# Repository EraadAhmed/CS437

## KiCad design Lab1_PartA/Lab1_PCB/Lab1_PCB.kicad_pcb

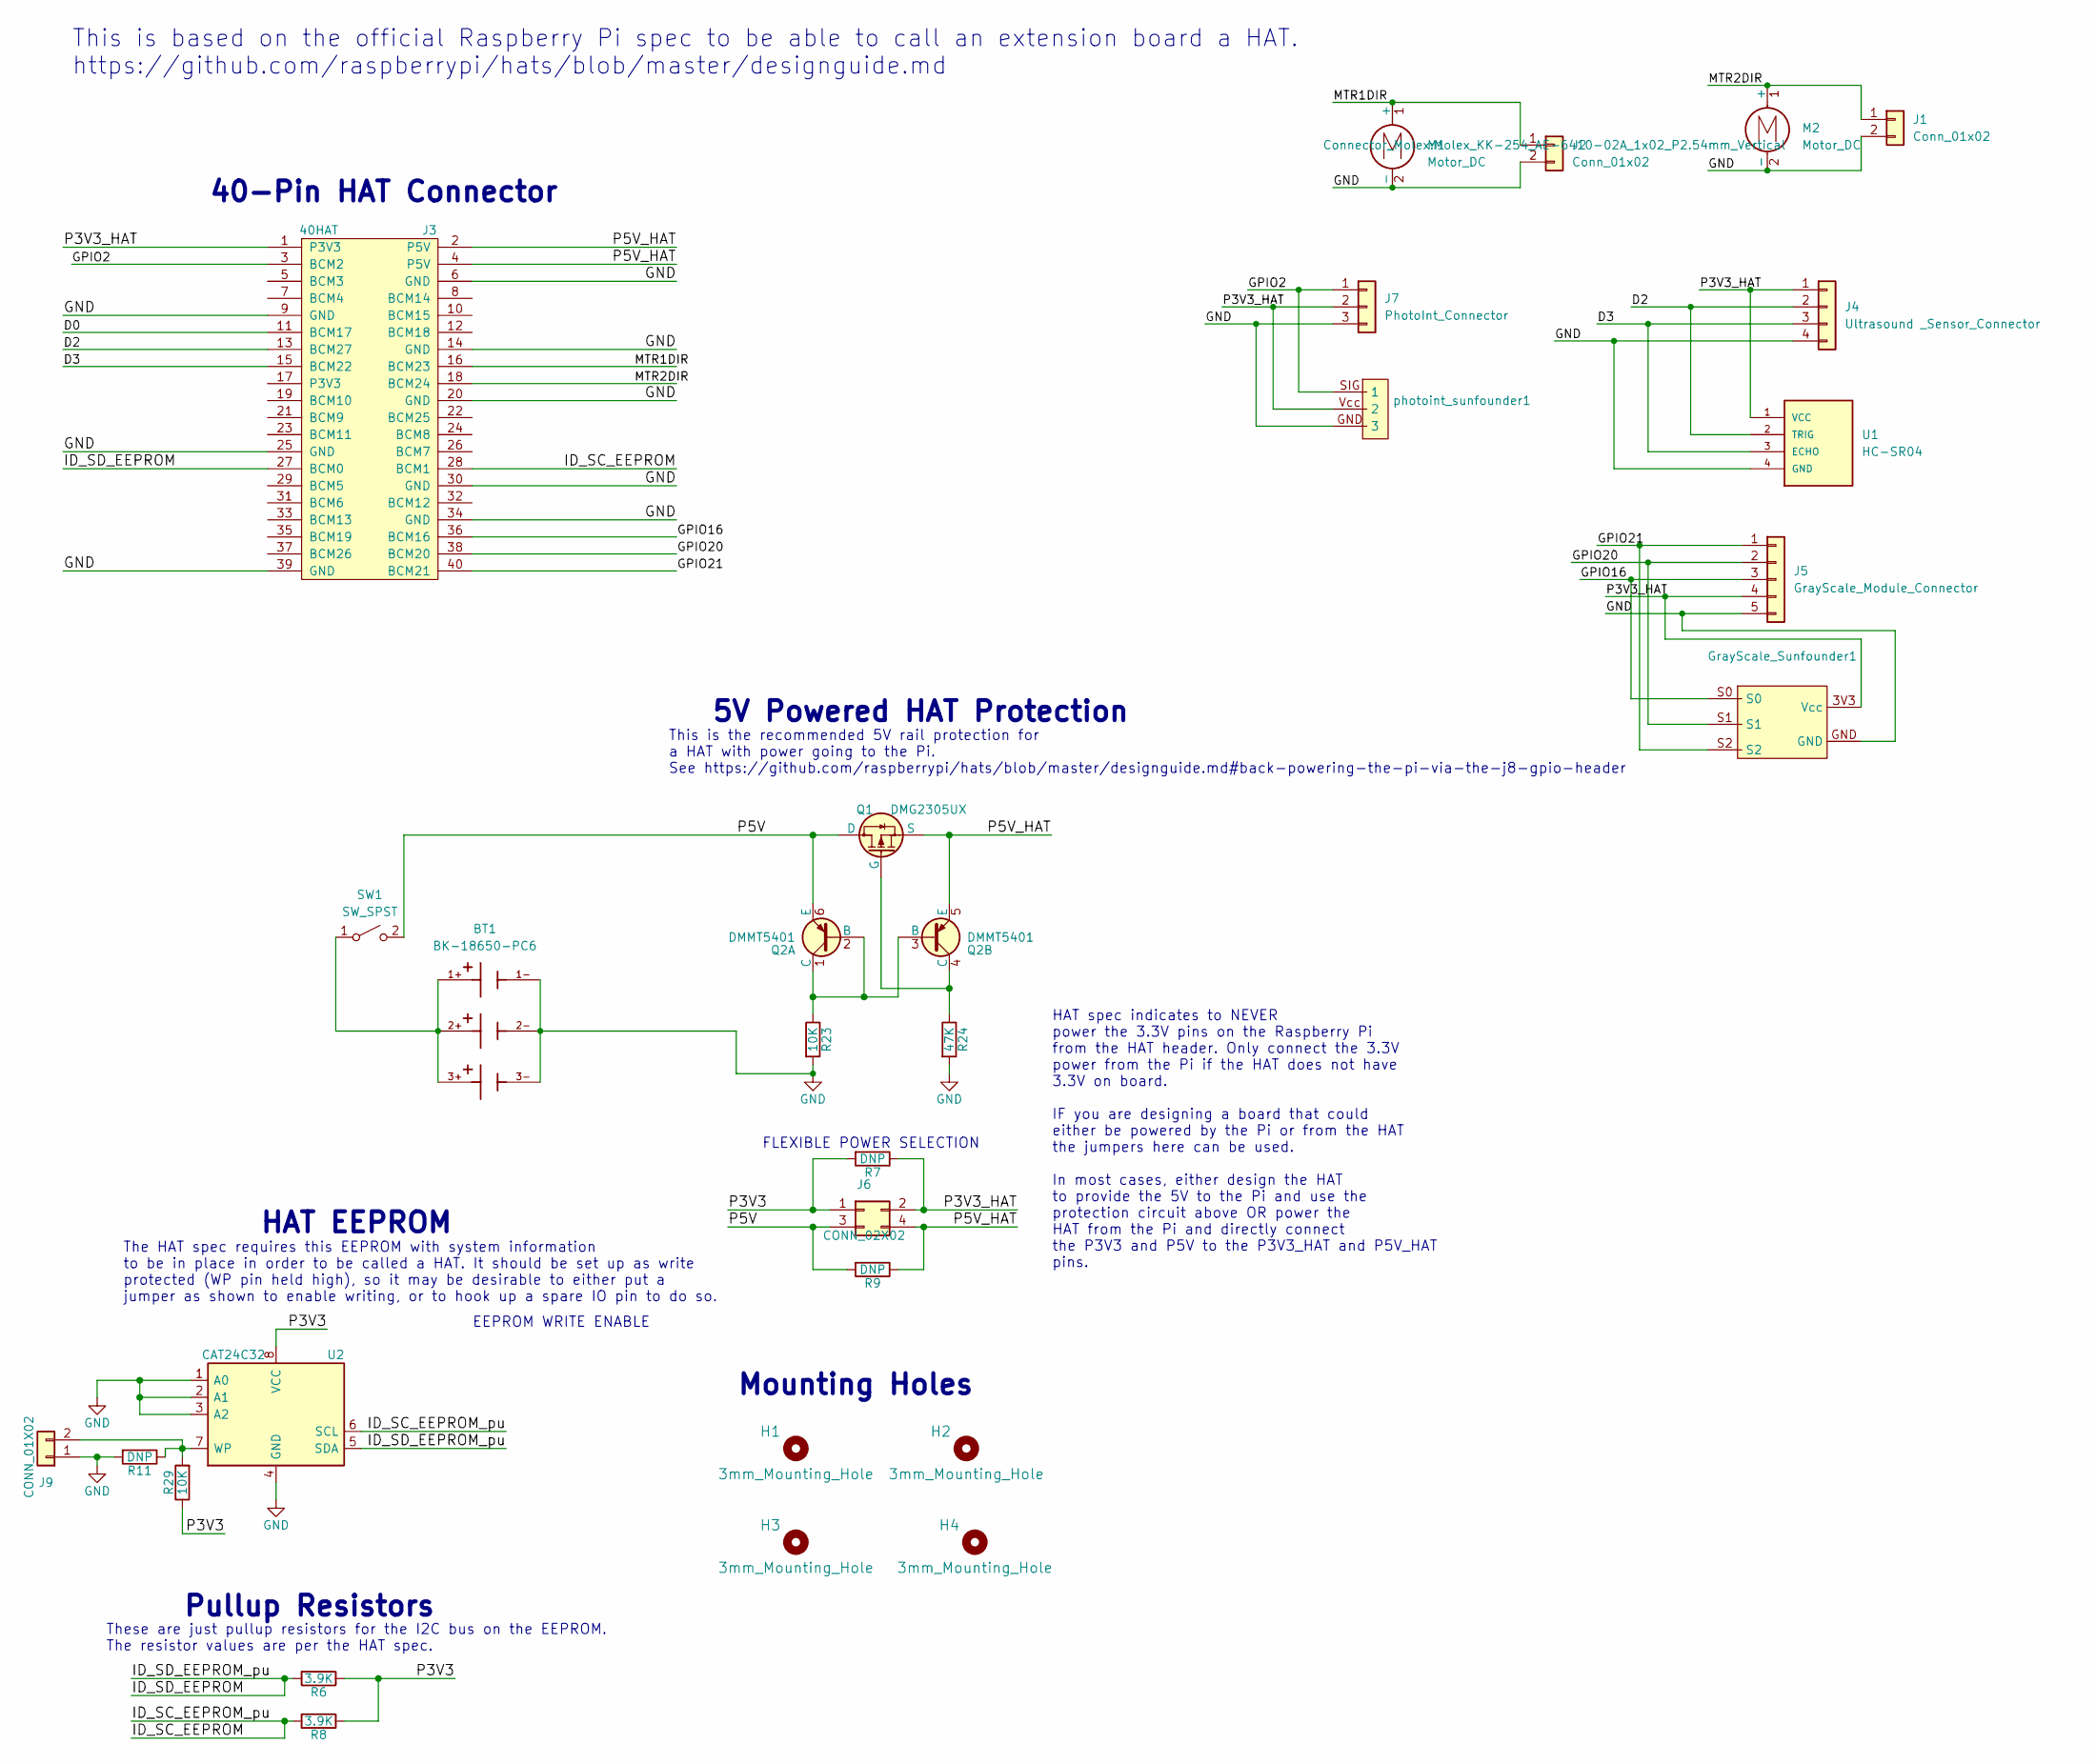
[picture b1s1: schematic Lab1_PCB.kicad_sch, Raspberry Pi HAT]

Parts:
BT1: BK-18650-PC6; BAT_BK-18650-PC6; PARTREV N
GrayScale_Sunfounder1: Sunfound_Grayscale
H1, H2, H3, H4: 3mm_Mounting_Hole; NPTH_3mm_ID
J1, J2: Conn_01x02; Molex_KK-254_AE-6410-02A_1x02_P2.54mm_Vertical
J3: 40HAT; PinSocket_2x20_P2.54mm_Vertical
J4: Ultrasound _Sensor_Connector; PinSocket_1x04_P1.00mm_Vertical
J5: GrayScale_Module_Connector; PinSocket_1x05_P1.00mm_Vertical
J6: CONN_02X02; PinHeader_2x02_P2.54mm_Vertical
J7: PhotoInt_Connector; PinSocket_1x03_P1.00mm_Vertical
J9: CONN_01X02; PinHeader_1x02_P2.54mm_Vertical
M1, M2: Motor_DC; DC_MOTOR
Q1: DMG2305UX; SOT-23
Q2: DMMT5401
R6, R8: 3.9K; R_0603_1608Metric_Pad0.84x1.00mm_HandSolder
R7, R9, R11: DNP; R_0603_1608Metric_Pad0.84x1.00mm_HandSolder
R23, R29: 10K; R_0603_1608Metric_Pad0.84x1.00mm_HandSolder
R24: 47K; R_0603_1608Metric_Pad0.84x1.00mm_HandSolder
SW1: SW_SPST; SW_DIP_SPSTx01_Slide_9.78x4.72mm_W7.62mm_P2.54mm
U1: HC-SR04; XCVR_HC-SR04
U2: CAT24C32; SOIC-8_3.9x4.9mm_P1.27mm
photoint_sunfounder1: Sunfounder_Photointerrupter

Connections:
/D0: J3.11 (BCM17)
/D2: J3.13 (BCM27), J4.2 (Trig), U1.2 (TRIG)
/D3: J3.15 (BCM22), J4.3 (ECHO), U1.3 (ECHO)
/GPIO2: J3.3 (BCM2), J7.1 (SIG), photoint_sunfounder1.SIG (1)
/GPIO16: GrayScale_Sunfounder1.S0, J3.36 (BCM16), J5.3 (S0)
/GPIO20: GrayScale_Sunfounder1.S1, J3.38 (BCM20), J5.2 (S1)
/GPIO21: GrayScale_Sunfounder1.S2, J3.40 (BCM21), J5.1 (S2)
/ID_SC_EEPROM: J3.28 (BCM1), R8.2, U2.6 (SCL)
/ID_SD_EEPROM: J3.27 (BCM0), R6.2, U2.5 (SDA)
/MTR1DIR: J2.1, J3.16 (BCM23), M1.1 (+)
/MTR2DIR: J1.1, J3.18 (BCM24), M2.1 (+)
/P3V3: J6.1, R6.1, R7.2, R8.1, R29.1, U2.8 (VCC)
/P3V3_HAT: GrayScale_Sunfounder1.3V3 (Vcc), J3.1 (P3V3), J4.1 (Vcc), J5.4 (3V3), J6.2, J7.2 (Vcc), R7.1, U1.1 (VCC), photoint_sunfounder1.Vcc (2)
/P5V: J6.3, Q1.3 (D), Q2.6 (E), R9.2, SW1.2 (B)
/P5V_HAT: J3.2 (P5V), J3.4 (P5V), J6.4, Q1.2 (S), Q2.5 (E), R9.1
GND: BT1.1-, BT1.2-, BT1.3-, GrayScale_Sunfounder1.GND, J1.2, J2.2, J3.6 (GND), J3.9 (GND), J3.14 (GND), J3.20 (GND), J3.25 (GND), J3.30 (GND), J3.34 (GND), J3.39 (GND), J4.4 (GND), J5.5 (GND), J7.3 (GND), J9.1, M1.2 (-), M2.2 (-), R11.2, R23.2, R24.2, U1.4 (GND), U2.1 (A0), U2.2 (A1), U2.3 (A2), U2.4 (GND), photoint_sunfounder1.GND (3)
unnamed: J9.2, R11.1, R29.2, U2.7 (WP)
unnamed: Q1.1 (G), Q2.4 (C), R24.1
unnamed: Q2.1 (C), Q2.2 (B), Q2.3 (B), R23.1
unnamed: BT1.1+, BT1.2+, BT1.3+, SW1.1 (A)

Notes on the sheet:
This is based on the official Raspberry Pi spec to be able to call an extension board a HAT. https://github.com/raspberrypi/hats/blob/master/designguide.md
This is the recommended 5V rail protection for a HAT with power going to the Pi. See https://github.com/raspberrypi/hats/blob/master/designguide.md#back-powering-the-pi-via-the-j8-gpio-header
The HAT spec requires this EEPROM with system information to be in place in order to be called a HAT. It should be set up as write protected (WP pin held high), so it may be desirable to either put a jumper as shown to enable writing, or to hook up a spare IO pin to do so.
5V Powered HAT Protection
HAT spec indicates to NEVER power the 3.3V pins on the Raspberry Pi from the HAT header. Only connect the 3.3V power from the Pi if the HAT does not have 3.3V on board. IF you are designing a board that could either be powered by the Pi or from the HAT the jumpers here can be used. In most cases, e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
40-Pin HAT Connector
Mounting Holes
HAT EEPROM
These are just pullup resistors for the I2C bus on the EEPROM. The resistor values are per the HAT spec.
EEPROM WRITE ENABLE
FLEXIBLE POWER SELECTION
Pullup Resistors

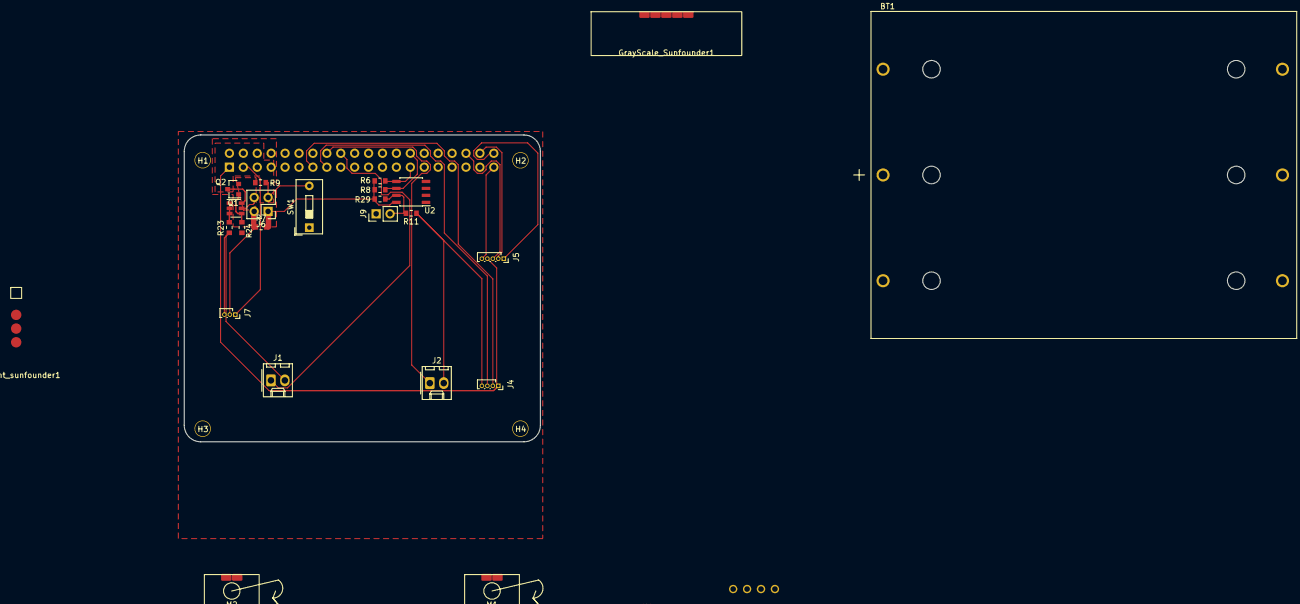
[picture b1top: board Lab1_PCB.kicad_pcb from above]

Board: 4 copper layers, 65.0 x 56.0 mm, 30 parts (1 on the bottom side), 19 nets.

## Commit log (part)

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2025-09-16 repo setup for lab1 eahme2 :
2025-09-16 part B folder
2025-09-17 computer vision work started eahme2
2025-09-18 progress on Hybrid A star, provisional finishing of the computer vision part
2025-09-19 A* done need to debug and put together
2025-09-20 main.py created needs to do work on it, car_control and computer_vision need clean up
2025-09-20 saad current work
2025-09-20 changes made for computer_vison and main
2025-09-20 changes maid to computer vision constants
2025-09-20 current
2025-09-20 made some changes to car_control
2025-09-21 computer vision changes to make it work
2025-09-21 more changes made to computer_vision.py
2025-09-21 computer vision changes made
2025-09-21 computer vision provisionally working
2025-09-22 changes made to files car_control and comp_vision
2025-09-22 cleanup
2025-09-22 ai slop
2025-09-22 do whatever you want (more test cases) - Eraad)
2025-09-22 current - Saad
2025-09-22 almost done, debugging the detect and drive
2025-09-22 last commit for the night
2025-09-22 main2 ftw
2025-09-22 small changes to main2
2025-09-22 still trying to perfect realworld testing
2025-09-22 pushing before further work
2025-09-23 eraad last commit
2025-09-23 integrated change
2025-09-23 yesterday's unfinished business
2025-09-23 idk xd
2025-09-23 tuner
2025-09-23 final
2025-09-23 updated ignore
2025-09-28 starting bluetooth control
2025-09-28 chris andrews sucks
2025-09-28 debugging battery level
2025-09-28 debugging temp
2025-09-28 debug.txt
2025-09-28 added battery health information
2025-09-28 modded to pi socket to give proper value
2025-09-28 made changes to pi socket
2025-09-30 controls added
2025-09-30 testing bluetooth controls
2025-09-30 testing bluetooth controls #2
2025-09-30 steering testing
2025-10-01 should be complete for bluetooth
2025-10-01 added mcaesar givens
2025-10-01 Added iot-lab-2 to Lab2
2025-10-02 working on wifi server
2025-10-03 web app
2025-10-03 fixed import
2025-10-03 fixed imports
2025-10-03 fixed website
2025-10-27 lab 2 finished
2025-10-27 lab3 part 1 and 2
2025-10-31 added bash screenshots
2025-11-03 updated gitignore for logs
2025-11-03 added logs
2025-11-03 added log texts
2025-11-03 added lab 3 figures
2025-11-08 lab 4 started
2025-11-10 lots of secret stuff kept unsecurely lmao
2025-11-13 pushing greengrass artifact component code 4 part2
2025-11-14 part 2 setup done, now need to test and debug
2025-11-16 changes made to 1.7 client emulator
2025-11-16 changes to main.py
2025-11-16 deployment for part 2 workign now, need to test
2025-11-16 processing buddy
2025-11-16 debugging p2
2025-11-17 pushed commit
2025-11-17 part 2 almost cooked
2025-11-17 ok dokie
2025-12-09 done with v1
2025-12-10 version 2 with sleep functionality
2025-12-11 watever
2025-12-11 updated formatting
2025-12-11 version done
2025-12-12 finally done
